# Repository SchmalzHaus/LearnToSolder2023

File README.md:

# LearnToSolder2018

## Introduction

For the past couple years, Deanna Schmalz has designed a simple circuit board which we then use to teach learn to solder classes. We  make enough boards and buy enough parts to teach all of the 4th graders at Glen Lake Elementary School in Minnetonka Minnesota, USA how to solder.

This site contains all of the information related to this year's Learn To Solder board. If you want to learn more about how to solder, if you want to know what you need to purchase so you can solder at home, or if you want to make more of these boards for yourself or your organization, this site has everything you'll need.

If you want to reach Brian Schmalz (brian@schmalzaus.com) or Deanna (deanna@schmalzhaus.com) to ask us any questions, please do so. 

All text files and designs on this site are Open Source. You are free to use these files and do whatever you wish with them.

## LearnToSolder 2018 Kit Contents

* Qty 1 Circuit Board - with pre-programmed PIC12F1572 CPU soldered on
* Qty 2 Switches
* Qty 2 Switch caps (various colors)
* Qty 2 Red LEDs
* Qty 2 Green LEDs
* Qty 2 Yellow LEDs
* Qty 2 Blue LEDs
* Qty 1 CR2032 Battery Holder
* Qty 1 CR2032 Battery
* Qty 2 random value through hole resistors (for Octopus eyebrows)

## Tools

To solder electronic kits together, you will need (at a minimum)

### Soldering Iron

We do not recommend buying a soldering iron unless it is 'temperature controlled'. This means you get to set the tip temperature with a knob or buttons, and the iron will only heat up as much as it needs to in order to maintain that temperature. Using a non-temp controlled iron has, in our experience, led to lots of frustration and failed kits.

This is the iron we recommend, as we've had great experience with it and it is very inexpensive : [http://www.hobbyking.com/hobbyking/store/__19240__Soldering_Station_with_Adjustable_Heat_Range_US_Warehouse_.html]

You can also by this same type of iron from many other places, including Amazon and Ebay, but the price tends to be a bit higher. Some of the companies listed below under Other Soldering Kits also sell tools like irons.

### Solder

For beginners, we strongly recommend using leaded solder (rather than lead-free). The safety risk is very minimal (just be sure to wash your hands with soap when you are done) and it is far, far easier to get good soldered joints with leaded solder when you're just starting to learn soldering. You can buy leaded electronic solder at many on-line stores like SparkFun [https://www.sparkfun.com/products/9161] or Adafruit [https://www.adafruit.com/products/1886]. Make sure to buy 60/40 or 63/37 (those numbers represent the ratio of tin to lead in the solder) electronic solder - there are other solders out there (like silver solder for jewelry for example) that won't work for electronics.

### Brass Sponge

When you buy your iron, buy a bras sponge if the iron doesn't already come with it. These are much better than the watter sponge that comes with the iron for cleaning the tip of the soldering iron.

### Wire Cutter

All of the companies listed below sell small wire cutters, or you can get them locally at hardware stores too. The best kind is something that will allow you to cut off wires flush with the board - sometimes called 'flush cutters'. For example [https://www.sparkfun.com/products/11952] or [https://www.adafruit.com/products/152]

### Other tools

There are lots of other tools you can get to help you while solder. Third-hands can be very useful. Needle nose pliers, solder suckers, magnifying glasses, solder wick, wire strippers, etc.

## Kit Assembly Process (overview)

There are only a couple steps to assembling this kit, as it is very simple. If you have done soldering before, you can just walk through this overview of the steps to complete your kit. If you want to learn more about how to do the actual soldering of a joint, the following websites and resources will give you plenty of background materials and explanations:

https://learn.sparkfun.com/tutorials/how-to-solder---through-hole-soldering

http://www.howtogeek.com/63630/how-to-use-a-soldering-iron-a-beginners-guide/

https://cdn-learn.adafruit.com/downloads/pdf/adafruit-guide-excellent-soldering.pdf

### Steps:

1. Solder the eight LEDs. Follow the color guide on the circuit board. Long lead (wire) goes into square hole. You sometimes have to wiggle the LEDs a bit to get them to press all the way flat down on the top side of the board due to a thick spot on the LED leads. Bend the leads apart on the back side to keep the LEDs in place as you solder the LED wires on the back side of the board. Clip the excess leads on the back of the board once soldered.

2. Insert the two switches into the board. Make sure all parts go into the board from the top side (with the thick white lines) to the back side. The switches snap down into the board - you sometimes have to press them in hard to get them to snap. But be careful - sometimes the pins come somewhat bent and pressing them down hard will bend them further if all four are not in the holes as you press down. Solder the four pins of each switch on the back side of the board. Snap the two switch caps down on the switches.

3. Insert the battery holder to the front of the board, being careful to align the outline of the battery hold to the white outline on the top of the board (there is a square tab on the battery holder than needs to match up to the square tab part of the outline). While holding the battery holder into the board, flip it over and solder both pins.

4. Insert the two eyebrow resistors. They are not part of the circut but are just for looks. Bend each lead of the reisstor so that the leads go through the board and the resistor sits flush on the board. Solder the leads on the back side of the board and clip excess lead length.

4. Insert the battery into the holder, flat shiny + side up. Press the buttons to see your LEDs light. If you hold down a button, the octopus will display a pattern.

## Other Soldering Kits

There are SO MANY kits available today, it's impossible to list all of them, or even the good ones. If you do a Google search for "electronic soldering kit" you will find lots of them out there. Some are easier than others, and some come with great instructions (and some don't).

We buy a lot of high quality soldering kits from the following on-line companies:

Evil Mad Scientist [http://shop.evilmadscientist.com/]
* Their Boldport Buggy is excellent [http://shop.evilmadscientist.com/]
* The Flickery Flame is a great beginner kit [http://shop.evilmadscientist.com/productsmenu/793]

Spark Fun Electronics [https://www.sparkfun.com/]
* They have a whole catagory of 'kits', some of which are soldering kits [https://www.sparkfun.com/categories/157]
* The SparkFun Simon Says - Through-Hole kit is really fun [https://www.sparkfun.com/products/10547]

Adafruit [https://www.adafruit.com/]
* The Drawdio is quite fun [https://www.adafruit.com/categories/28]
* Their Minty Boost is actually quite useful [https://www.adafruit.com/products/14]

SeeedStudio [http://www.seeedstudio.com/]
* Their 4-Soldering Zoo Kit looks super cute [https://www.seeedstudio.com/item_detail.html?p_id=1950]

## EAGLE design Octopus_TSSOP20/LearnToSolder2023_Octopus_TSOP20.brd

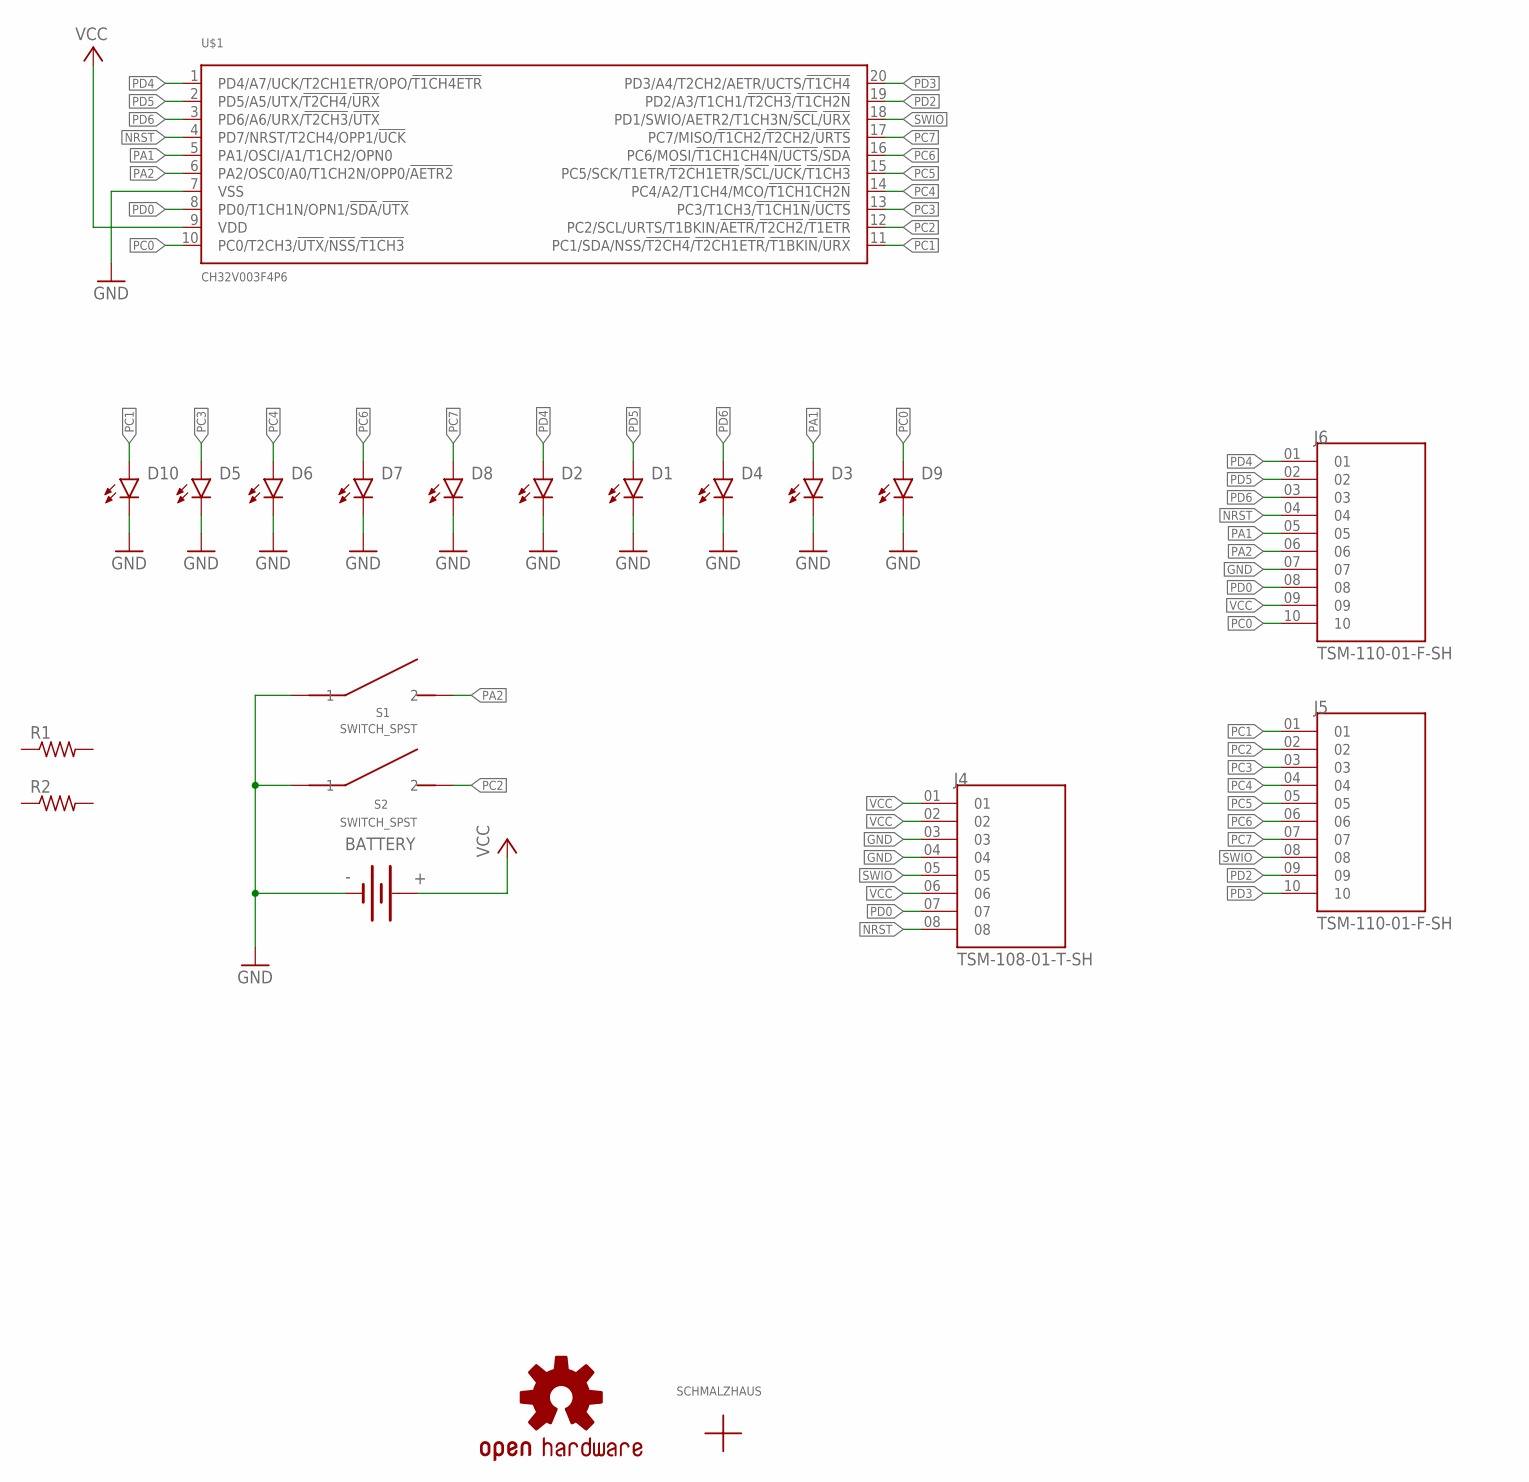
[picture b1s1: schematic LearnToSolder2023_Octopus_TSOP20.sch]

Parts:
BATTERY: BATTERY20PTH; BATTCOM_20MM_PTH
D1, D2, D3, D4, D5, D6, D7, D8, D9, D10: LED5MM
J4: TSM-108-01-T-SH; SAMTEC_TSM-108-01-T-SH
J5, J6: TSM-110-01-F-SH; SAMTEC_TSM-110-01-F-SH
LOGO1: OSHW-LOGOMINI; OSHW-LOGO-MINI
R1, R2: R-US_0309/12; 0309/12
S1, S2: SWITCH_SPST; OMRON-12MMX12MM_SPST-B3F-4000
U$1: CH32V003F4P6; TSSOP20
U$3: SCHMALZHAUSSCHMALZHAUS_SMALL; SCHMALZHAUS_SMALL

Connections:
GND: BATTERY.2 (-), D1.K (C), D2.K (C), D3.K (C), D4.K (C), D5.K (C), D6.K (C), D7.K (C), D8.K (C), D9.K (C), D10.K (C), J4.03, J4.04, J6.07, S1.1, S1.2 (1), S2.1, S2.2 (1), U$1.7 (VSS)
NRST: J4.08, J6.04, U$1.4 (PD7/NRST/T2CH4/OPP1/!UCK!)
PA1: D3.A, J6.05, U$1.5 (PA1/OSCI/A1/T1CH2/OPN0)
PA2: J6.06, S1.3 (2), S1.4 (2), U$1.6 (PA2/OSC0/A0/T1CH2N/OPP0/!AETR2!)
PC0: D9.A, J6.10, U$1.10 (PC0/T2CH3/!UTX!/!NSS!/!T1CH3!)
PC1: D10.A, J5.01, U$1.11 (PC1/SDA/NSS/!T2CH4!/!T2CH1ETR!/!T1BKIN!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)
PC2: J5.02, S2.3 (2), S2.4 (2), U$1.12 (PC2/SCL/URTS/T1BKIN/!AETR!/!T2CH2!/!T1E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)
PC3: D5.A, J5.03, U$1.13 (PC3/T1CH3/!T1CH1N!/!UCTS!)
PC4: D6.A, J5.04, U$1.14 (PC4/A2/T1CH4/MCO/!T1CH1CH2N!)
PC5: J5.05, U$1.15 (PC5/SCK/T1ETR/!T2CH1ETR!/!SCL!/!UCK!/!T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)
PC6: D7.A, J5.06, U$1.16 (PC6/MOSI/!T1CH1CH4N!/!UCTS!/!SDA!)
PC7: D8.A, J5.07, U$1.17 (PC7/MISO/!T1CH2!/!T2CH2!/!URTS!)
PD0: J4.07, J6.08, U$1.8 (PD0/T1CH1N/OPN1/!SDA!/!UTX!)
PD2: J5.09, U$1.19 (PD2/A3/T1CH1/!T2CH3!/!T1CH2N!)
PD3: J5.10, U$1.20 (PD3/A4/T2CH2/AETR/UCTS/!T1CH4!)
PD4: D2.A, J6.01, U$1.1 (PD4/A7/UCK/T2CH1ETR/OPO/!T1CH4ETR!)
PD5: D1.A, J6.02, U$1.2 (PD5/A5/UTX/!T2CH4!/!URX!)
PD6: D4.A, J6.03, U$1.3 (PD6/A6/URX/!T2CH3!/!UTX!)
SWIO: J4.05, J5.08, U$1.18 (PD1/SWIO/AETR2/T1CH3N/!SCL!/!URX!)
VCC: BATTERY.1 (+), J4.01, J4.02, J4.06, J6.09, U$1.9 (VDD)

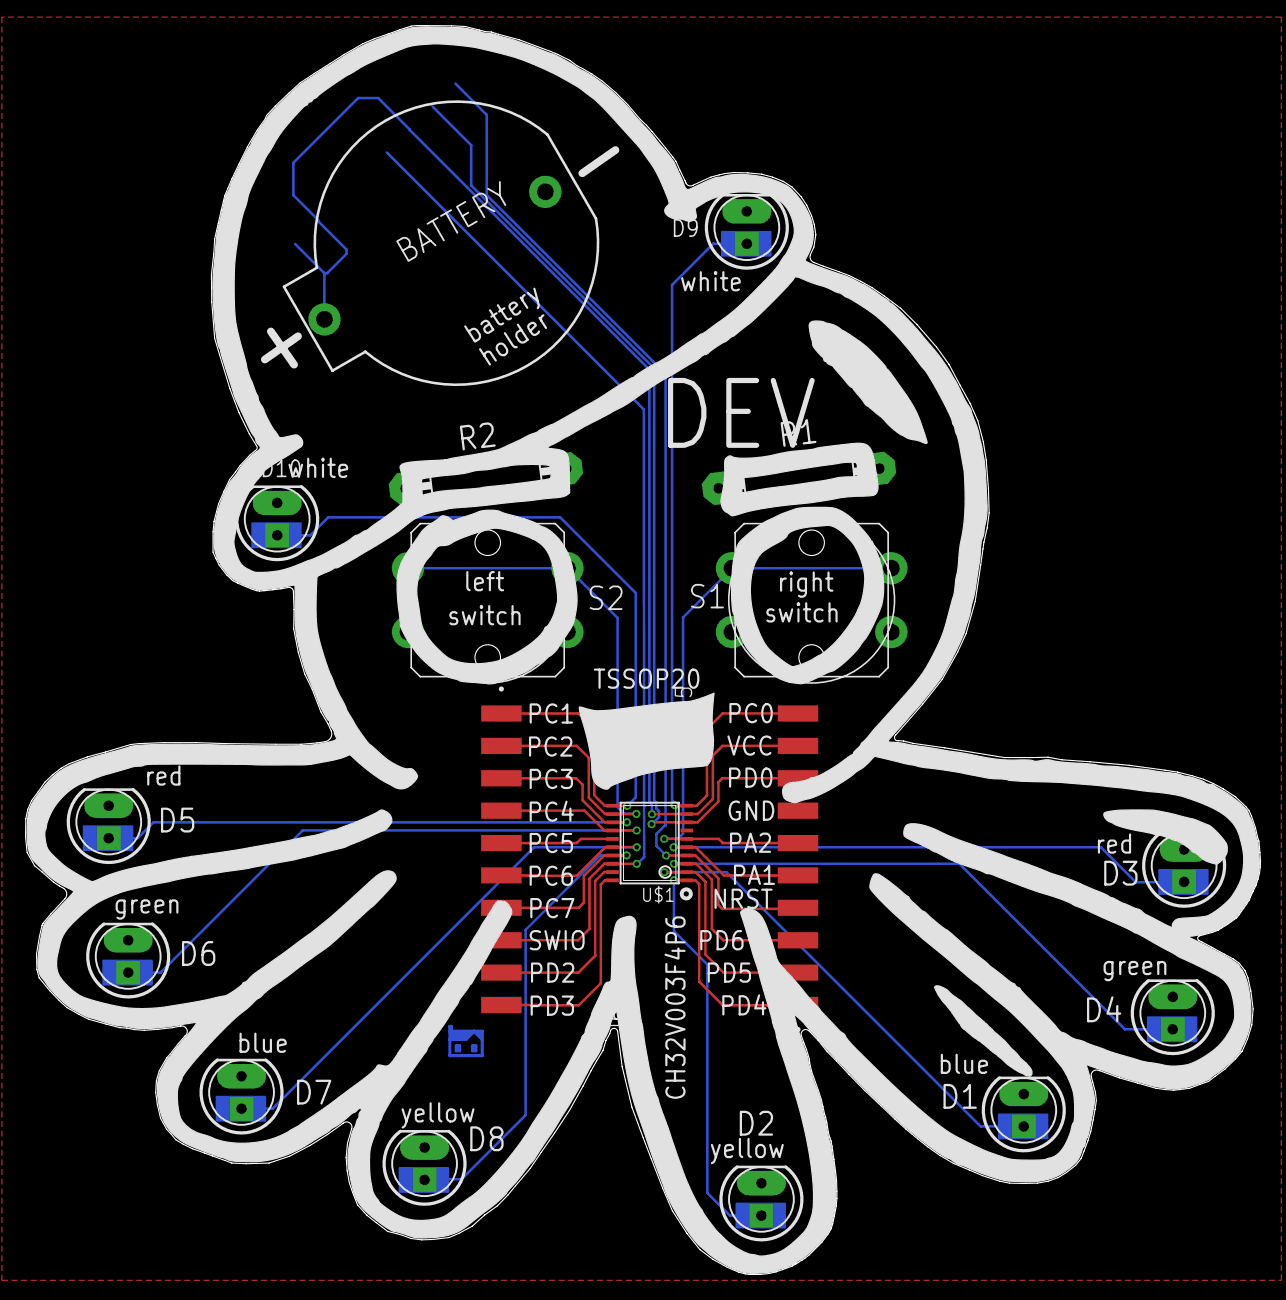
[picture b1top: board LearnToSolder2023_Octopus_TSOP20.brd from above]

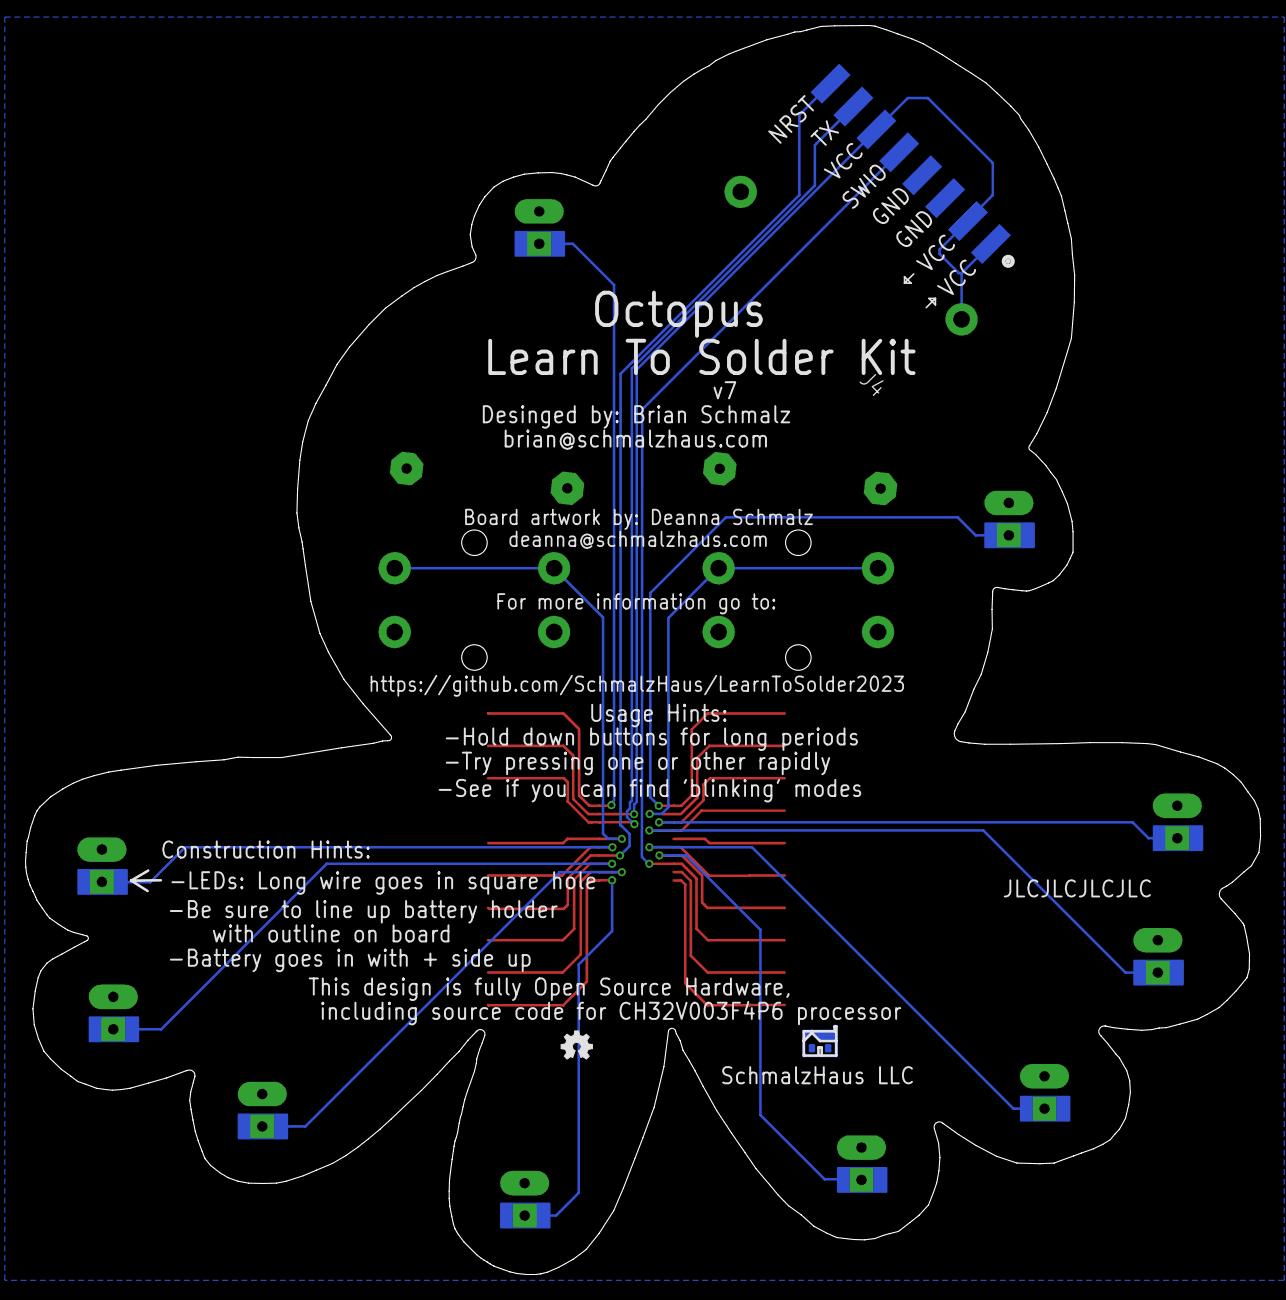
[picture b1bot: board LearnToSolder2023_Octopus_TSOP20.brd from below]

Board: 2 copper layers, 96.9 x 97.9 mm, 21 parts (3 on the bottom side), 20 nets.

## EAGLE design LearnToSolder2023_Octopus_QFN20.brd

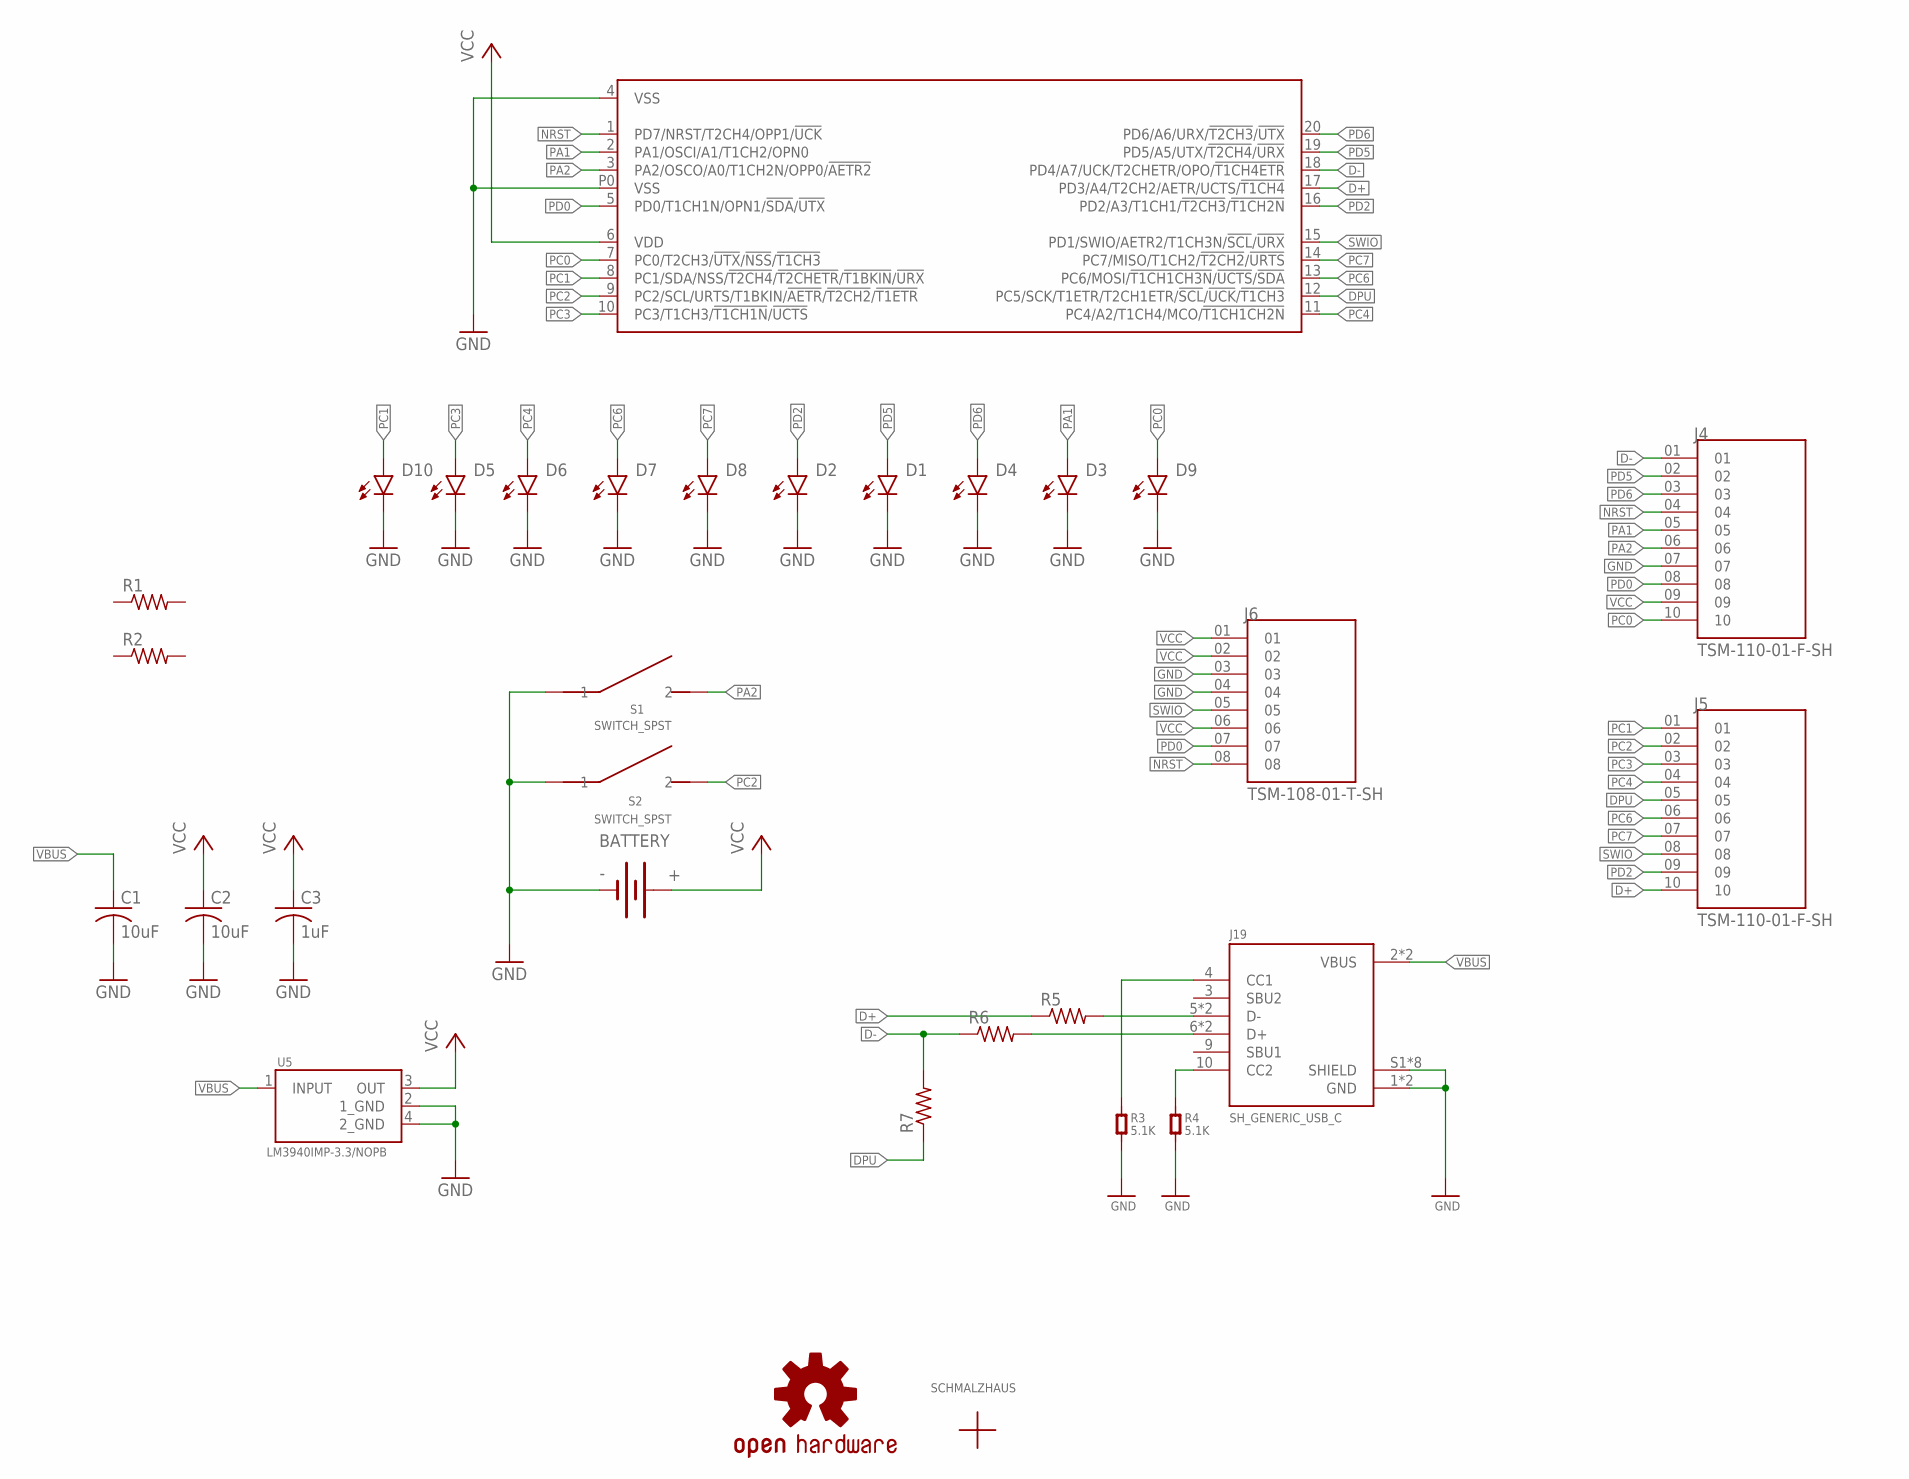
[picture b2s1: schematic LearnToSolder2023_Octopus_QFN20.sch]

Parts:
BATTERY: BATTERY20PTH; BATTCOM_20MM_PTH
C1, C2: 10uF; C0603
C3: 1uF; C0603
D1, D2, D3, D4, D5, D6, D7, D8, D9, D10: LED5MM
J4, J5: TSM-110-01-F-SH; SAMTEC_TSM-110-01-F-SH
J6: TSM-108-01-T-SH; SAMTEC_TSM-108-01-T-SH
J19: SH_GENERIC_USB_C
LOGO1: OSHW-LOGOMINI; OSHW-LOGO-MINI
R1, R2: R-US_0309/12; 0309/12
R3, R4: 5.1K; R0603
R5, R6, R7: R-US_R0603; R0603
S1, S2: SWITCH_SPST; OMRON-12MMX12MM_SPST-B3F-4000
U5: TEXAS_INSTRUMENTS_LM3940IMP-3_3-NOPBTEXAS_INSTRUM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; TEXAS_INSTRUMENTS_LM3940IMP-3_3-NOPB_0
U$1: CH32V003F4U6; QFN20
U$3: SCHMALZHAUSSCHMALZHAUS_SMALL; SCHMALZHAUS_SMALL

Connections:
D+: J5.10, R5.1, U$1.17 (PD3/A4/T2CH2/AETR/UCTS/!T1CH4!)
D-: J4.01, R6.1, R7.2, U$1.18 (PD4/A7/UCK/T2CHETR/OPO/!T1CH4ETR!)
DPU: J5.05, R7.1, U$1.12 (PC5/SCK/T1ETR/T2CH1ETR/!SCL!/!UCK!/!T1C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)
GND: BATTERY.2 (-), C1.2, C2.2, C3.2, D1.K (C), D2.K (C), D3.K (C), D4.K (C), D5.K (C), D6.K (C), D7.K (C), D8.K (C), D9.K (C), D10.K (C), J4.07, J6.03, J6.04, J19.1 (GND), J19.12 (GND), J19.S1 (SHIELD), J19.S2 (SHIELD), J19.S3 (SHIELD), J19.S4 (SHIELD), J19.S5 (SHIELD), J19.S6 (SHIELD), J19.S7 (SHIELD), J19.S8 (SHIELD), R3.1, R4.1, S1.1, S1.2 (1), S2.1, S2.2 (1), U5.2 (1_GND), U5.4 (2_GND), U$1.4 (VSS), U$1.P0 (VSS)
unnamed: J19.4 (CC1), R3.2
unnamed: J19.10 (CC2), R4.2
unnamed: J19.5 (D-), J19.7 (D-), R5.2
unnamed: J19.6 (D+), J19.8 (D+), R6.2
NRST: J4.04, J6.08, U$1.1 (PD7/NRST/T2CH4/OPP1/!UCK!)
PA1: D3.A, J4.05, U$1.2 (PA1/OSCI/A1/T1CH2/OPN0)
PA2: J4.06, S1.3 (2), S1.4 (2), U$1.3 (PA2/OSCO/A0/T1CH2N/OPP0/!AETR2!)
PC0: D9.A, J4.10, U$1.7 (PC0/T2CH3/!UTX!/!NSS!/!T1CH3!)
PC1: D10.A, J5.01, U$1.8 (PC1/SDA/NSS/!T2CH4!/!T2CHETR!/!T1BKIN!/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)
PC2: J5.02, S2.3 (2), S2.4 (2), U$1.9 (PC2/SCL/URTS/T1BKIN/!AETR!/!T2CH2!/!T1E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)
PC3: D5.A, J5.03, U$1.10 (PC3/T1CH3/!T1CH1N!/!UCTS!)
PC4: D6.A, J5.04, U$1.11 (PC4/A2/T1CH4/MCO/!T1CH1CH2N!)
PC6: D7.A, J5.06, U$1.13 (PC6/MOSI/!T1CH1CH3N!/!UCTS!/!SDA!)
PC7: D8.A, J5.07, U$1.14 (PC7/MISO/T1CH2/!T2CH2!/!URTS!)
PD0: J4.08, J6.07, U$1.5 (PD0/T1CH1N/OPN1/!SDA!/!UTX!)
PD2: D2.A, J5.09, U$1.16 (PD2/A3/T1CH1/!T2CH3!/!T1CH2N!)
PD5: D1.A, J4.02, U$1.19 (PD5/A5/UTX/!T2CH4!/!URX!)
PD6: D4.A, J4.03, U$1.20 (PD6/A6/URX/!T2CH3!/!UTX!)
SWIO: J5.08, J6.05, U$1.15 (PD1/SWIO/AETR2/T1CH3N/!SCL!/!URX!)
VBUS: C1.1, J19.2 (VBUS), J19.11 (VBUS), U5.1 (INPUT)
VCC: BATTERY.1 (+), C2.1, C3.1, J4.09, J6.01, J6.02, J6.06, U5.3 (OUT), U$1.6 (VDD)

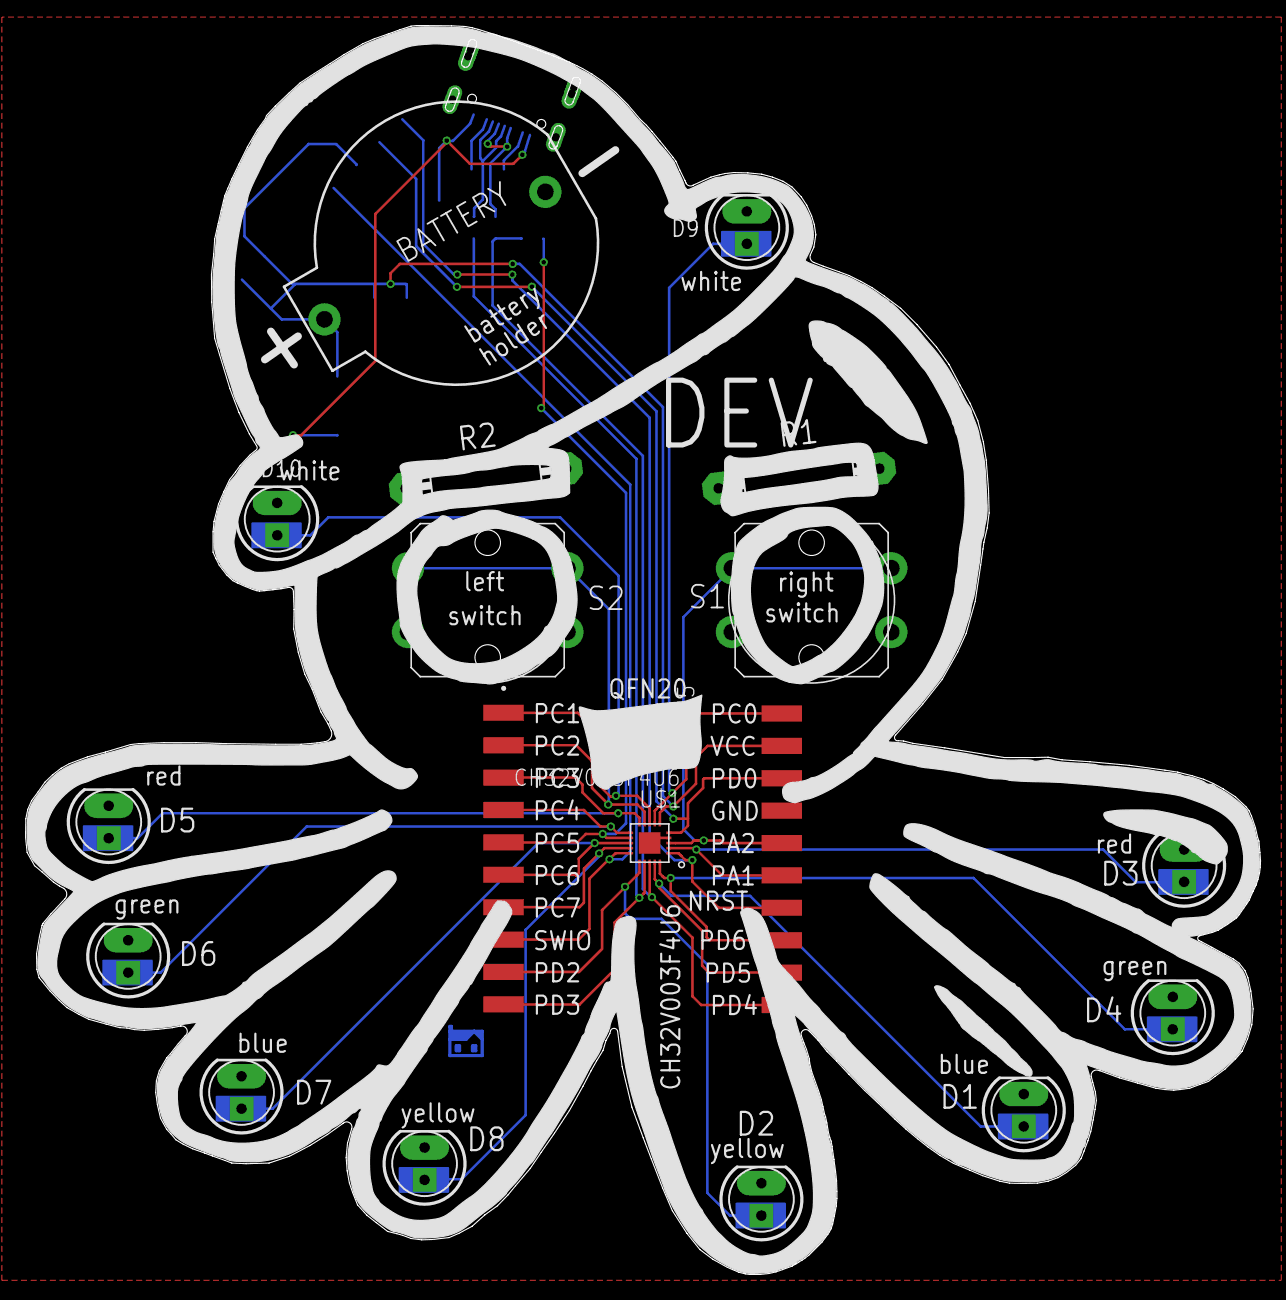
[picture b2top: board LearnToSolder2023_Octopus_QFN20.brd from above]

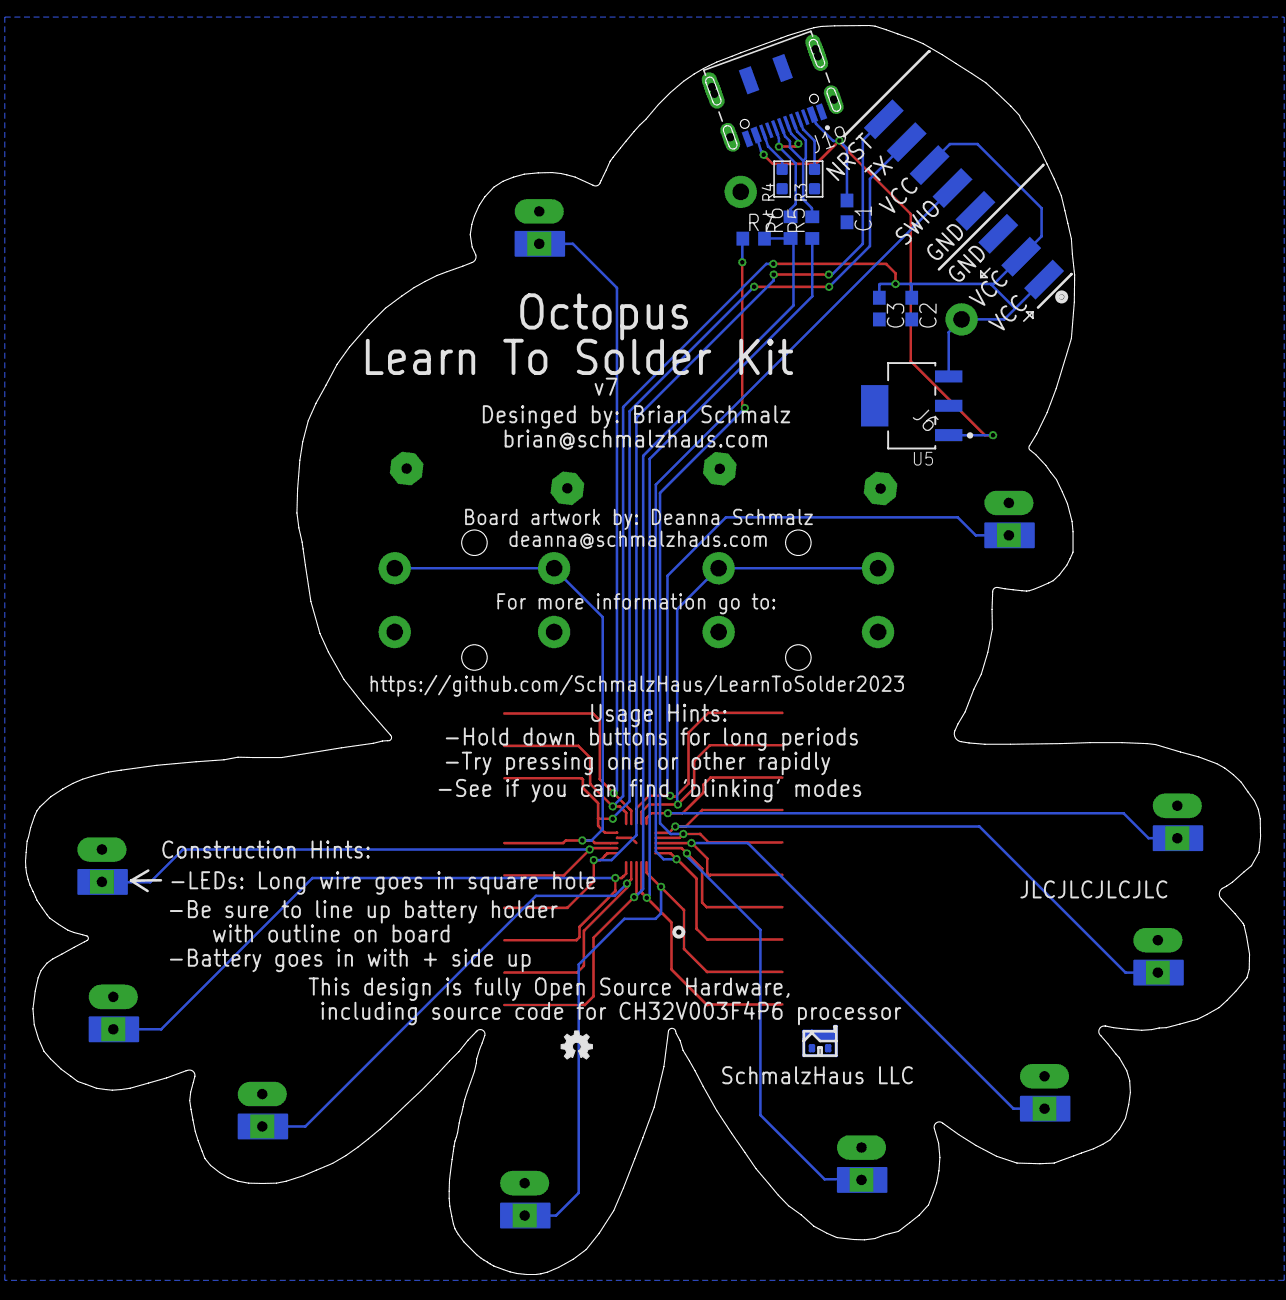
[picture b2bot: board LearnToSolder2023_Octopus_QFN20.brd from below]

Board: 2 copper layers, 96.9 x 97.9 mm, 31 parts (13 on the bottom side), 25 nets.

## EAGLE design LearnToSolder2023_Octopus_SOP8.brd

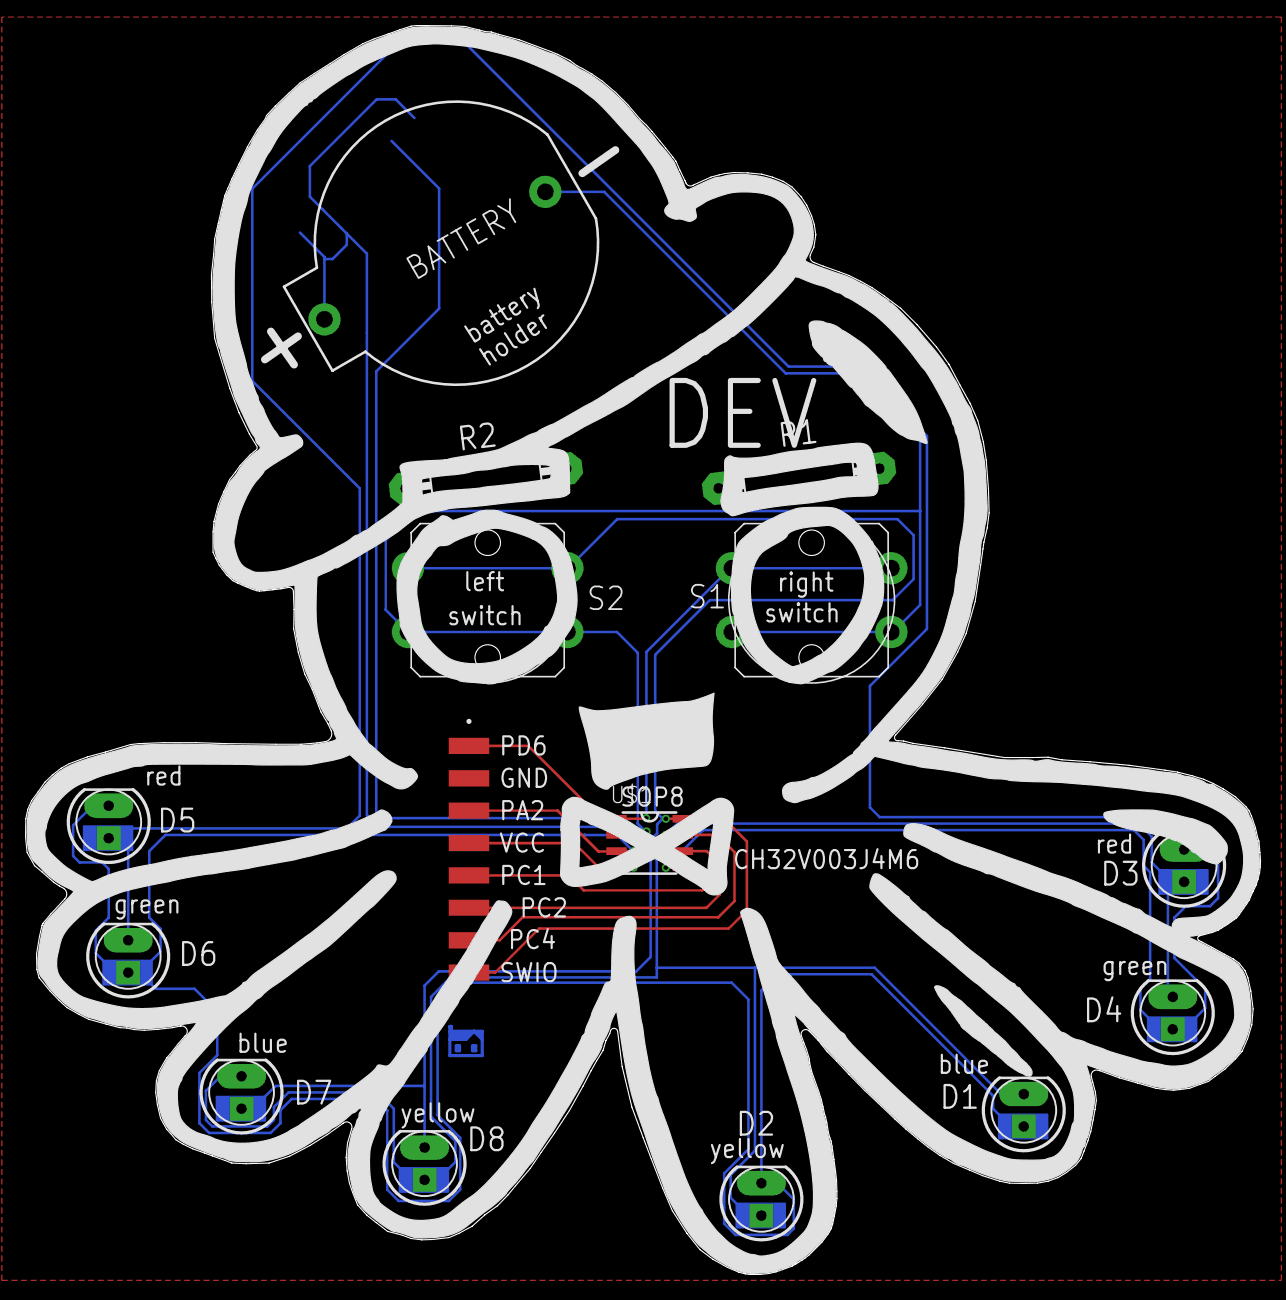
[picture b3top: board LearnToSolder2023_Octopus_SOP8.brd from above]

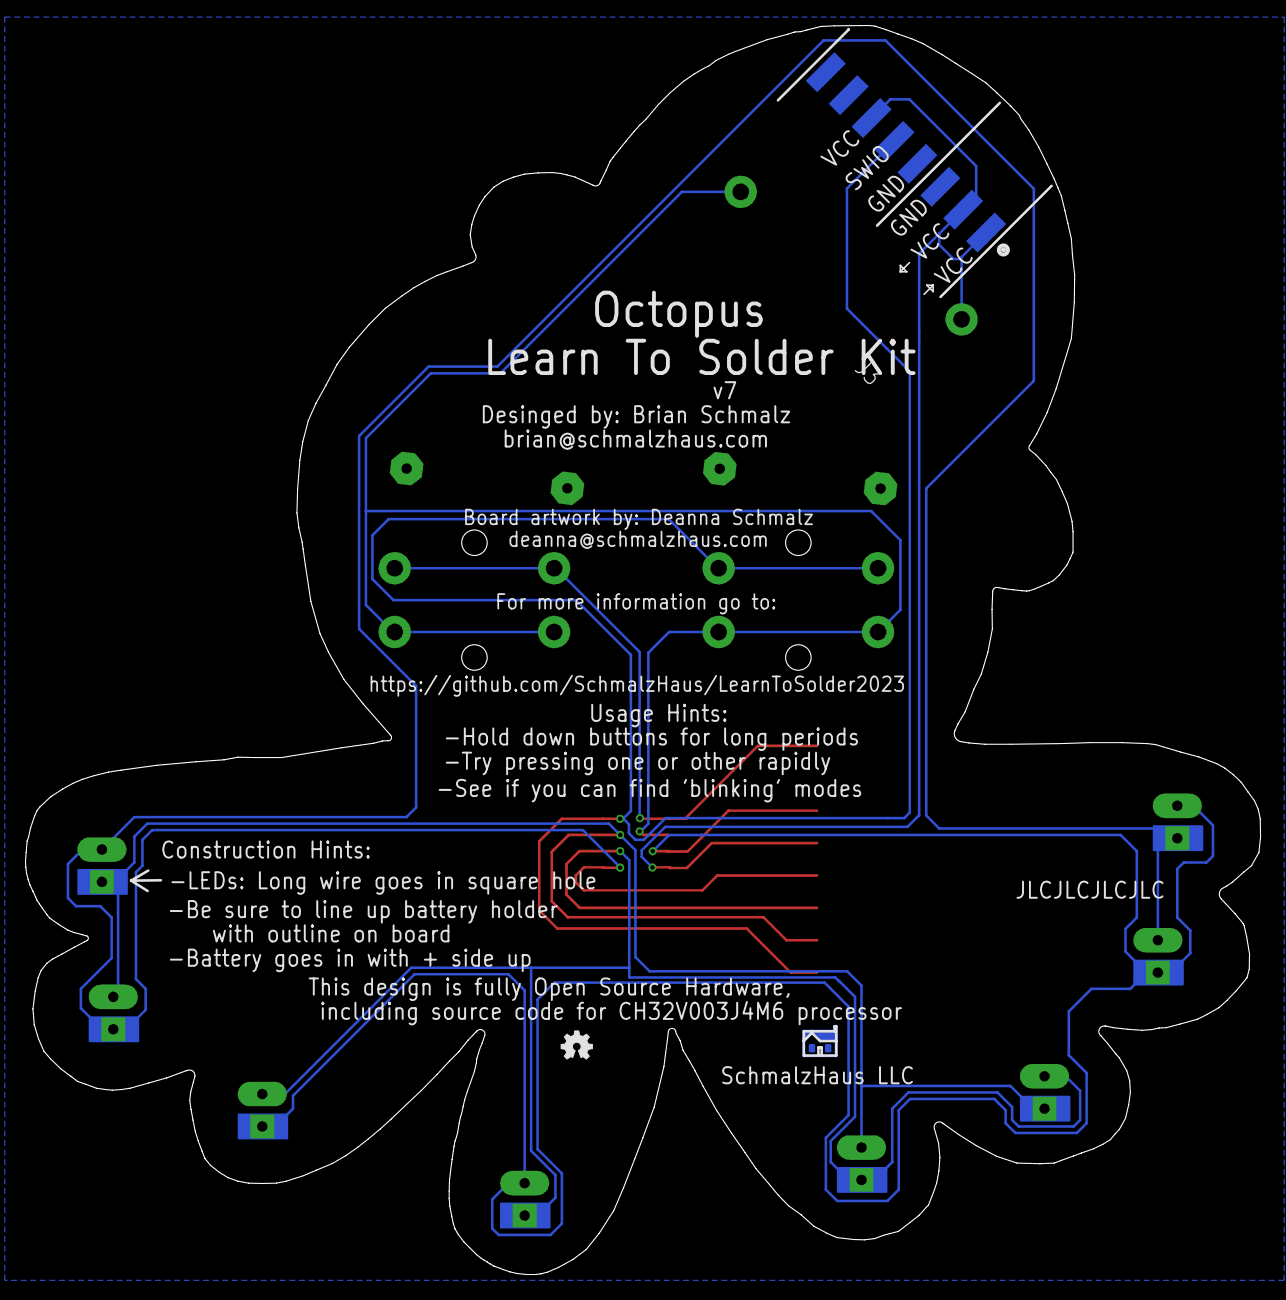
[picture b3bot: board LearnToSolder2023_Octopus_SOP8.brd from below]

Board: 2 copper layers, 96.9 x 97.9 mm, 18 parts (3 on the bottom side), 8 nets.

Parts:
BATTERY: BATTCOM_20MM_PTH
D1, D2, D3, D4, D5, D6, D7, D8: LED5MM
J2, J3: TSM-108-01-T-SH; SAMTEC_TSM-108-01-T-SH
LOGO1: OSHW-LOGOMINI; OSHW-LOGO-MINI
R1, R2: 0309/12
S1, S2: SWITCH_SPST; OMRON-12MMX12MM_SPST-B3F-4000
U$1: CH32V003J4M6; SOP8
U$3: SCHMALZHAUSSCHMALZHAUS_SMALL; SCHMALZHAUS_SMALL

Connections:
GND: BATTERY.2, J2.02, J3.03, J3.04, S1.1, S1.2, S2.1, S2.2, U$1.2
PA2: D1.A, D2.K, D5.K, D6.A, J2.03, U$1.3
PC1: D3.K, D4.A, D5.A, D6.K, J2.05, U$1.5
PC2: D1.K, D2.A, D7.K, D8.A, J2.06, U$1.6
PC4: D3.A, D4.K, D7.A, D8.K, J2.07, U$1.7
PD6: J2.01, S1.3, S1.4, U$1.1
SWIO: J2.08, J3.05, S2.3, S2.4, U$1.8
VCC: BATTERY.1, J2.04, J3.01, J3.02, J3.06, U$1.4

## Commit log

2023-06-05 First check in
2023-06-09 Updated QFN20 footprint to be 3x3 rather than 5x5. Reworked Octopus QFN20 board.
2023-06-19 Removed EAGLE backup files, added .gitignore
2023-06-19 Move everything into their own folders.

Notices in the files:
parts and their libraries:
SparkFun-Aesthetics: Licensing: Creative Commons ShareAlike 4.0 International - https://creativecommons.org/licenses/by-sa/4.0
